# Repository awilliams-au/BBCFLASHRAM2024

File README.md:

# BBCFLASHRAM2024
kicad files and software for a sideways RAM and FLASH ROM expansion board for a BBC Micro Model A or B.

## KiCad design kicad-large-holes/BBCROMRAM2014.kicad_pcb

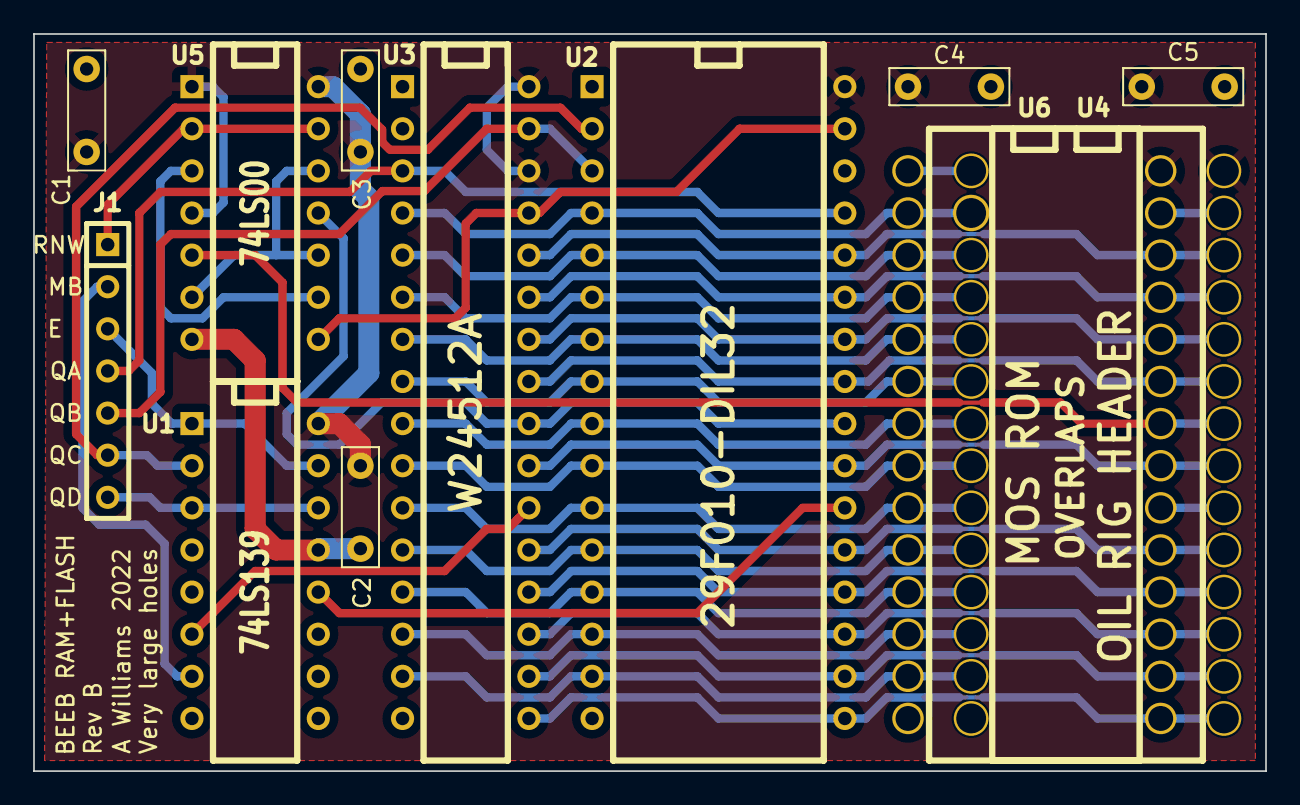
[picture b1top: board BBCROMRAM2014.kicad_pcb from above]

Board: 2 copper layers, 74.3 x 44.4 mm, 12 parts (0 on the bottom side), 41 nets.

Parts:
C1, C2, C3, C4, C5: 0.1uF; C_Rect_L7.0mm_W2.0mm_P5.00mm
J1: CON1; SIL-7
U1: 74LS139; DIP-16__300
U2: 29F010-DIL32; DIP-32__600
U3: W24512A; DIP-32__300
U4: OIL RIG HEADER; DIP-28__600
U5: 74LS00; DIP-14__300
U6: MOS ROM; DIP-28__600

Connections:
/A0: U2.12 (A0), U3.12 (A0), U4.10 (A0), U6.10 (A0)
/A1: U2.11 (A1), U3.11 (A1), U4.9 (A1), U6.9 (A1)
/A2: U2.10 (A2), U3.10 (A2), U4.8 (A2), U6.8 (A2)
/A3: U2.9 (A3), U3.9 (A3), U4.7 (A3), U6.7 (A3)
/A4: U2.8 (A4), U3.8 (A4), U4.6 (A4), U6.6 (A4)
/A5: U2.7 (A5), U3.7 (A5), U4.5 (A5), U6.5 (A5)
/A6: U2.6 (A6), U3.6 (A6), U4.4 (A6), U6.4 (A6)
/A7: U2.5 (A7), U3.5 (A7), U4.3 (A7), U6.3 (A7)
/A8: U2.27 (A8), U3.27 (A8), U4.25 (A8), U6.25 (A8)
/A9: U2.26 (A9), U3.26 (A9), U4.24 (A9), U6.24 (A9)
/A10: U2.23 (A10), U3.23 (A10), U4.21 (A10), U6.21 (A10)
/A11: U2.25 (A11), U3.25 (A11), U4.23 (A11), U6.23 (A11)
/A12: U2.4 (A12), U3.4 (A12), U4.2 (A12), U6.2 (A12)
/A13: U2.28 (A13), U3.28 (A13), U4.26 (A13), U6.26 (A13)
/D0: U2.13 (D0), U3.13 (D0), U4.11 (D0), U6.11 (D0)
/D1: U2.14 (D1), U3.14 (D1), U4.12 (D1), U6.12 (D1)
/D2: U2.15 (D2), U3.15 (D2), U4.13 (D2), U6.13 (D2)
/D3: U2.17 (D3), U3.17 (D3), U4.15 (D3), U6.15 (D3)
/D4: U2.18 (D4), U3.18 (D4), U4.16 (D4), U6.16 (D4)
/D5: U2.19 (D5), U3.19 (D5), U4.17 (D5), U6.17 (D5)
/D6: U2.20 (D6), U3.20 (D6), U4.18 (D6), U6.18 (D6)
/D7: U2.21 (D7), U3.21 (D7), U4.19 (D7), U6.19 (D7)
/E: J1.3 (E), U1.1 (E), U1.15 (E)
/MB: J1.2 (MB), U1.7 (O3)
/MCE: U4.20 (CE), U6.20 (CE)
/MOE: U4.22 (OE), U5.5, U6.22 (OE)
/MPGM: U4.27 (~PGM), U6.27 (~PGM)
/MVPP: U4.1 (VPP), U6.1 (VPP)
/NFLASHCS: U1.12 (O0), U2.22 (CE)
/NOE: U2.24 (OE), U3.24 (OE), U5.11
/NRAMCS: U1.6 (O2), U3.22 (NCS1)
/NWDS: U2.31 (WE), U3.29 (WE), U5.8
/QA: J1.4 (A), U2.29 (A14), U3.3 (A14)
/QB: J1.5 (B), U2.3 (A15), U3.31 (A15)
/QC: J1.6 (C), U1.2 (A0), U2.2 (A16)
/QD: J1.7 (D), U1.3 (A1), U1.14 (A0)
/RNW: J1.1 (rw), U5.2, U5.13
GND: C1.2, C2.2, C3.2, C4.2, C5.2, U1.8 (GND), U1.13 (A1), U2.16 (GND), U3.16 (GND), U4.14 (GND), U5.7 (GND), U6.14 (GND)
unnamed: U5.3, U5.9
unnamed: U5.6, U5.10, U5.12
VCC: C1.1, C2.1, C3.1, C4.1, C5.1, U1.16 (VCC), U2.32 (VCC), U3.30 (CS2), U3.32 (VCC), U4.28 (VCC), U5.1, U5.4, U5.14 (VCC), U6.28 (VCC)
